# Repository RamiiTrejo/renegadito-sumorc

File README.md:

## RENEGADITO

Renegadito es un Sumo RC, el cual fue diseñado con la intención de hacerlo competir en la Liga Nacional de Robotica

## CARACTERÍSTICAS
- Renegadito cuenta con:
- 2-Motor reductores JGA25-370 de 280 RPM
- 2- Puente H TA6586
- 1-ESP32
- 1-Bateria de Li-po 3s de 1050mAh
- Peso: 1.8Kg

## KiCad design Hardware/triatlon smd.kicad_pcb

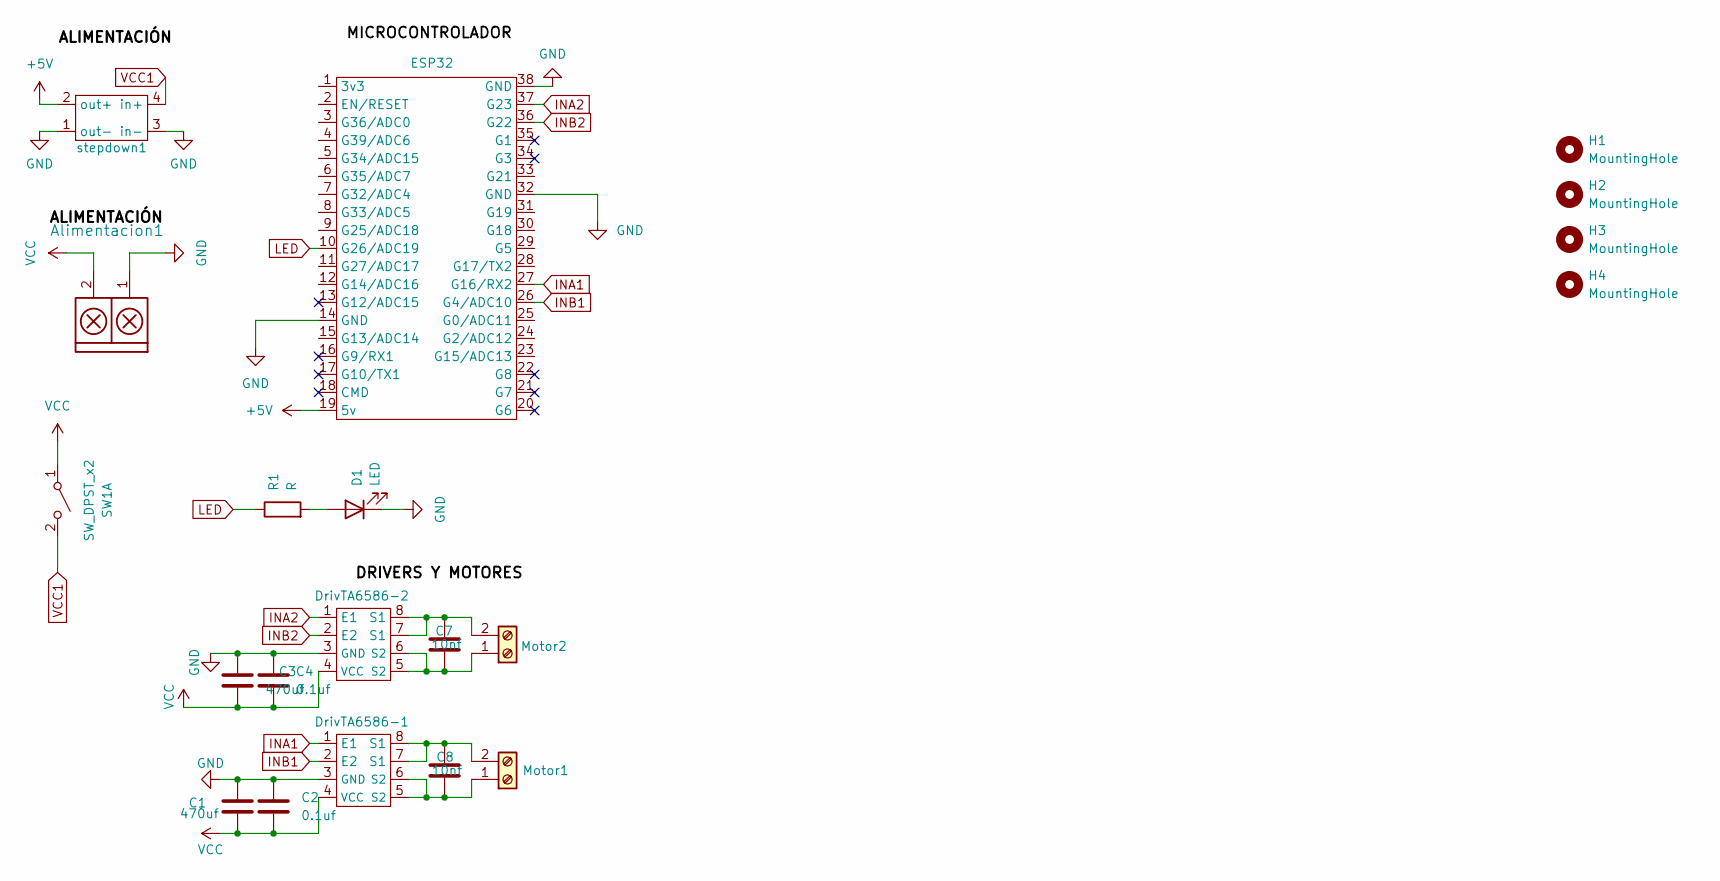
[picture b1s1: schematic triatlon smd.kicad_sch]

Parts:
Alimentacion1: TB_1X2; AMASS_XT60-F_1x02_P7.20mm_Vertical
C1, C3: 470uf; CP_Radial_D8.0mm_P3.80mm
C2, C4: 0.1uf; C_Disc_D5.0mm_W2.5mm_P5.00mm
C7, C8: 10nf; C_Disc_D5.0mm_W2.5mm_P5.00mm
D1: LED; LED_D5.0mm
DrivTA6586-1, DrivTA6586-2: DIP-8_W7.62mm
ESP32: esp32 38 pin usb-c
H1, H2, H3, H4: MountingHole; MountingHole_3.2mm_M3_DIN965
Motor1, Motor2: Screw_Terminal_01x02; BORNERA2_AZUL
R1: R; R_Axial_DIN0207_L6.3mm_D2.5mm_P7.62mm_Horizontal
SW1: SW_DPST_x2; SW_SPDT_TH_Vertical
stepdown1: STEPDOWN

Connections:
+5V: ESP32.19 (5v), stepdown1.2 (out+)
GND: Alimentacion1.1, C1.1, C2.1, C3.1, C4.1, D1.1 (K), DrivTA6586-1.3 (GND), DrivTA6586-2.3 (GND), ESP32.14 (GND), ESP32.32 (GND), ESP32.38 (GND), stepdown1.1 (out-), stepdown1.3 (in-)
INA1: DrivTA6586-1.1 (E1), ESP32.27 (G16/RX2)
INA2: DrivTA6586-2.1 (E1), ESP32.37 (G23)
INB1: DrivTA6586-1.2 (E2), ESP32.26 (G4/ADC10)
INB2: DrivTA6586-2.2 (E2), ESP32.36 (G22)
LED: ESP32.10 (G26/ADC19), R1.1
unnamed: D1.2 (A), R1.2
unnamed: C8.2, DrivTA6586-1.5 (S2), DrivTA6586-1.6 (S2), Motor1.1
unnamed: C8.1, DrivTA6586-1.7 (S1), DrivTA6586-1.8 (S1), Motor1.2
unnamed: C7.2, DrivTA6586-2.5 (S2), DrivTA6586-2.6 (S2), Motor2.1
unnamed: C7.1, DrivTA6586-2.7 (S1), DrivTA6586-2.8 (S1), Motor2.2
VCC: Alimentacion1.2, C1.2, C2.2, C3.2, C4.2, DrivTA6586-1.4 (VCC), DrivTA6586-2.4 (VCC), SW1.1 (A)
VCC1: SW1.2 (B), stepdown1.4 (in+)

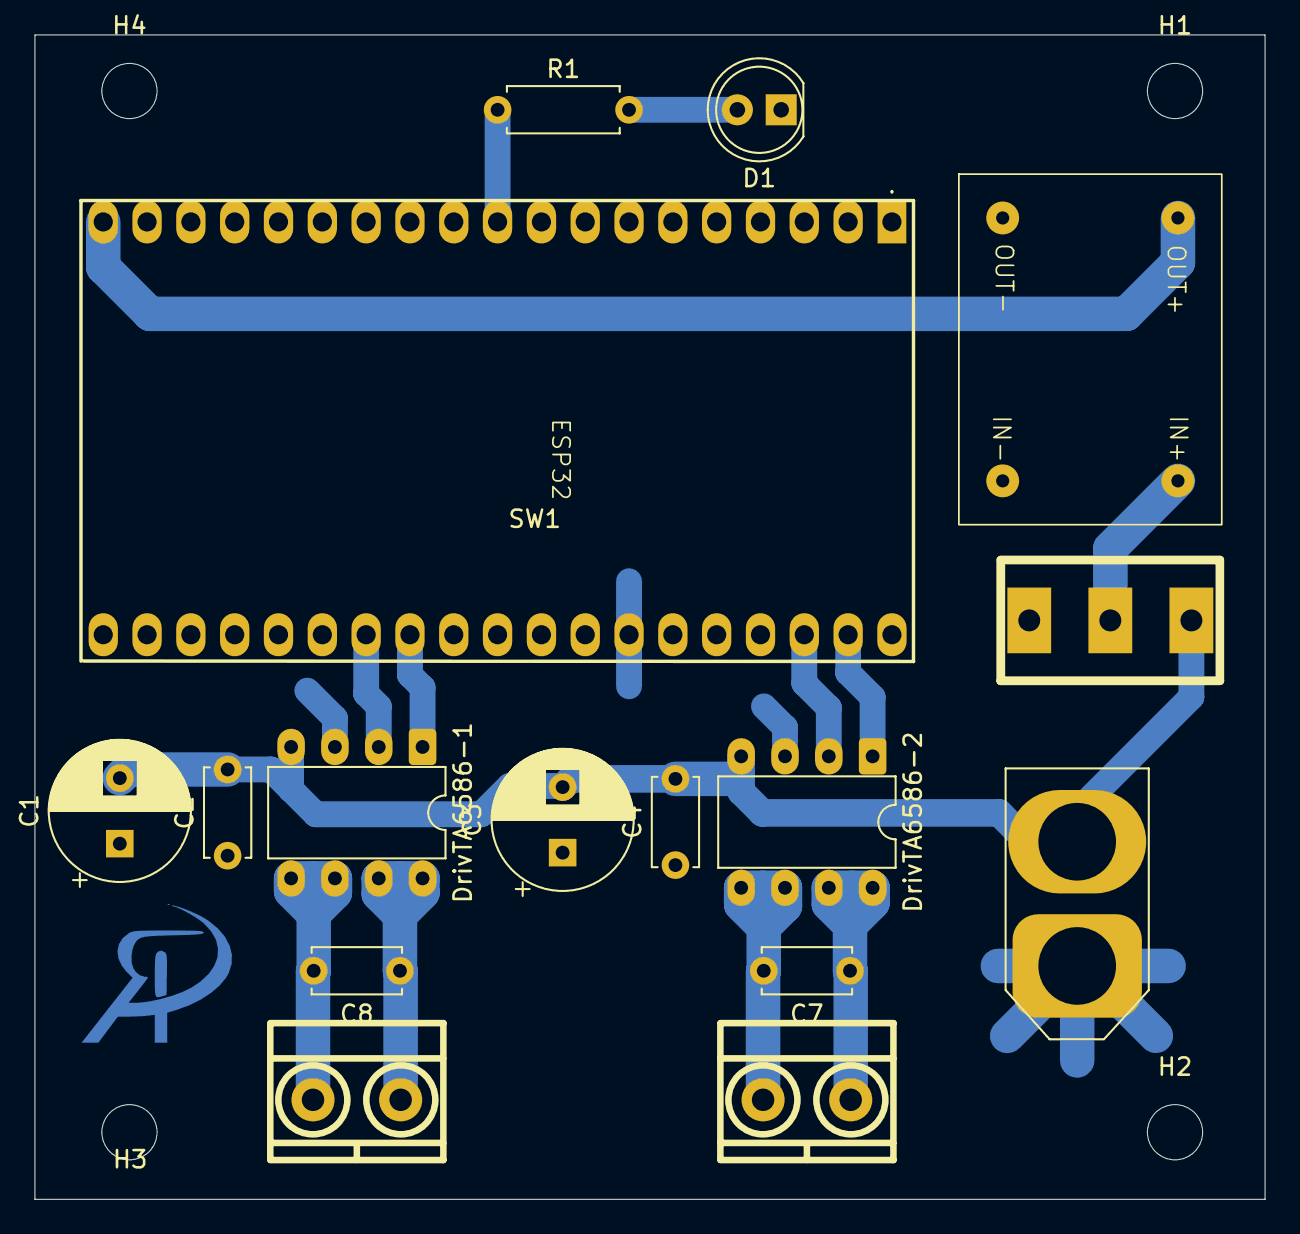
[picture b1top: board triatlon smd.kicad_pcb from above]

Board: 2 copper layers, 71.3 x 67.5 mm, 20 parts (0 on the bottom side), 14 nets.

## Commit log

2025-09-13 Update Kicad
2025-09-13 Kicad pro
2025-11-22 Add files via upload
    archivo kicad de renegado
